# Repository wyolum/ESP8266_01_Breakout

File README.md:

# ESP8266_01_Breakout
KiCad fork of https://github.com/sfgit/ESP8266-01-BREAKOUT

KiCad version of [technolomaniac]'s ESP8266-01 breakout board from here https://hackaday.io/project/5728-esp8266-01-breakout
and
https://github.com/sfgit/ESP8266-01-BREAKOUT

I also want to use it as a demo project while doing KiCad 101

License
-------
[CERN Open Hardware Licence v1.2 ]

[CERN Open Hardware Licence v1.2 ]:http://www.ohwr.org/attachments/2388/cern_ohl_v_1_2.txt

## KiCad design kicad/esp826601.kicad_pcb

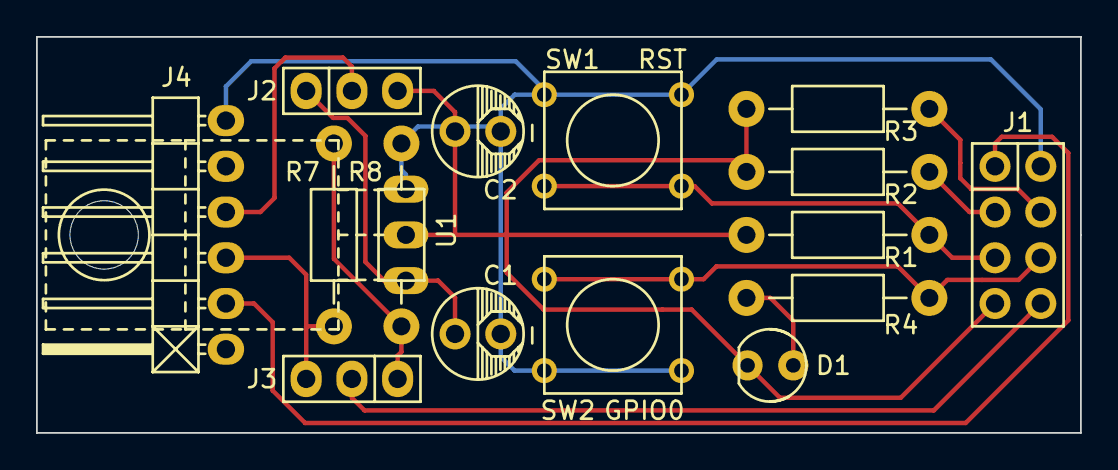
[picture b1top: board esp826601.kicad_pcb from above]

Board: 2 copper layers, 58.0 x 22.0 mm, 16 parts (0 on the bottom side), 13 nets.

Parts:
C1, C2: 10u; Capacitor5x6RM2.5
D1: LED; LED-3MM
J1: ESP8266-01; Pin_Header_Straight_2x04
J2: 5V0<>3V3; Pin_Header_Straight_1x03
J3: TX_LVL; Pin_Header_Straight_1x03
J4: FTDI; Pin_Header_Angled_1x06
R1, R2, R3, R4: 10k; Resistor_Horizontal_RM10mm
R7: 1k; Resistor_Horizontal_RM10mm
R8: 1k8; Resistor_Horizontal_RM10mm
SW1: RST; SW_PUSH_SMALL
SW2: GPIO0; SW_PUSH_SMALL
U1: LD1117AV33; TO-220_Neutral123_Horizontal_LS

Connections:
+3V3: C2.1, D1.2, J1.7, J2.3, R1.1, R2.1, R3.1, U1.2
+5V: C1.1, J2.1, U1.3
/CH_PD-A: J1.3, R2.2
/GPIO0-A: J1.6, R4.2, SW2.1
/GPIO2-A: J1.4, R3.2
/RST-A: J1.5, R1.2, SW1.2
/TX-PC: J1.8, J3.2
/TX_PC-A-DIV: J3.1, R7.2, R8.1
/USB_SER/RX_PC-A: J1.1, J4.2
/USB_SER/TX_PC-A: J3.3, J4.3, R7.1
/USB_SER/VIN: J2.2, J4.4
GND: C1.2, C2.2, J1.2, J4.6, R8.2, SW1.1, SW2.2, U1.1
unnamed: D1.1, R4.1

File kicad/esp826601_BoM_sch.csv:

Reference, Value, Footprint, Datasheet
J1,ESP8266-01,esp8266:Pin_Header_Straight_2x04,
R2,10k,esp8266:Resistor_Horizontal_RM10mm,
R1,10k,esp8266:Resistor_Horizontal_RM10mm,
R3,10k,esp8266:Resistor_Horizontal_RM10mm,
SW1,RST,esp8266:SW_PUSH_SMALL,
J3,TX_LVL,esp8266:Pin_Header_Straight_1x03,
R4,10k,esp8266:Resistor_Horizontal_RM10mm,
D1,LED,esp8266:LED-3MM,
SW2,GPIO0,esp8266:SW_PUSH_SMALL,
R7,1k,esp8266:Resistor_Horizontal_RM10mm,
R8,1k8,esp8266:Resistor_Horizontal_RM10mm,
J4,FTDI,esp8266:Pin_Header_Angled_1x06,
J2,5V0<>3V3,esp8266:Pin_Header_Straight_1x03,
U1,LD1117AV33,esp8266:TO-220_Neutral123_Horizontal_LS,
C1,10u,esp8266:Capacitor5x6RM2.5,
C2,10u,esp8266:Capacitor5x6RM2.5,

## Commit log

2015-06-19 work in progress
